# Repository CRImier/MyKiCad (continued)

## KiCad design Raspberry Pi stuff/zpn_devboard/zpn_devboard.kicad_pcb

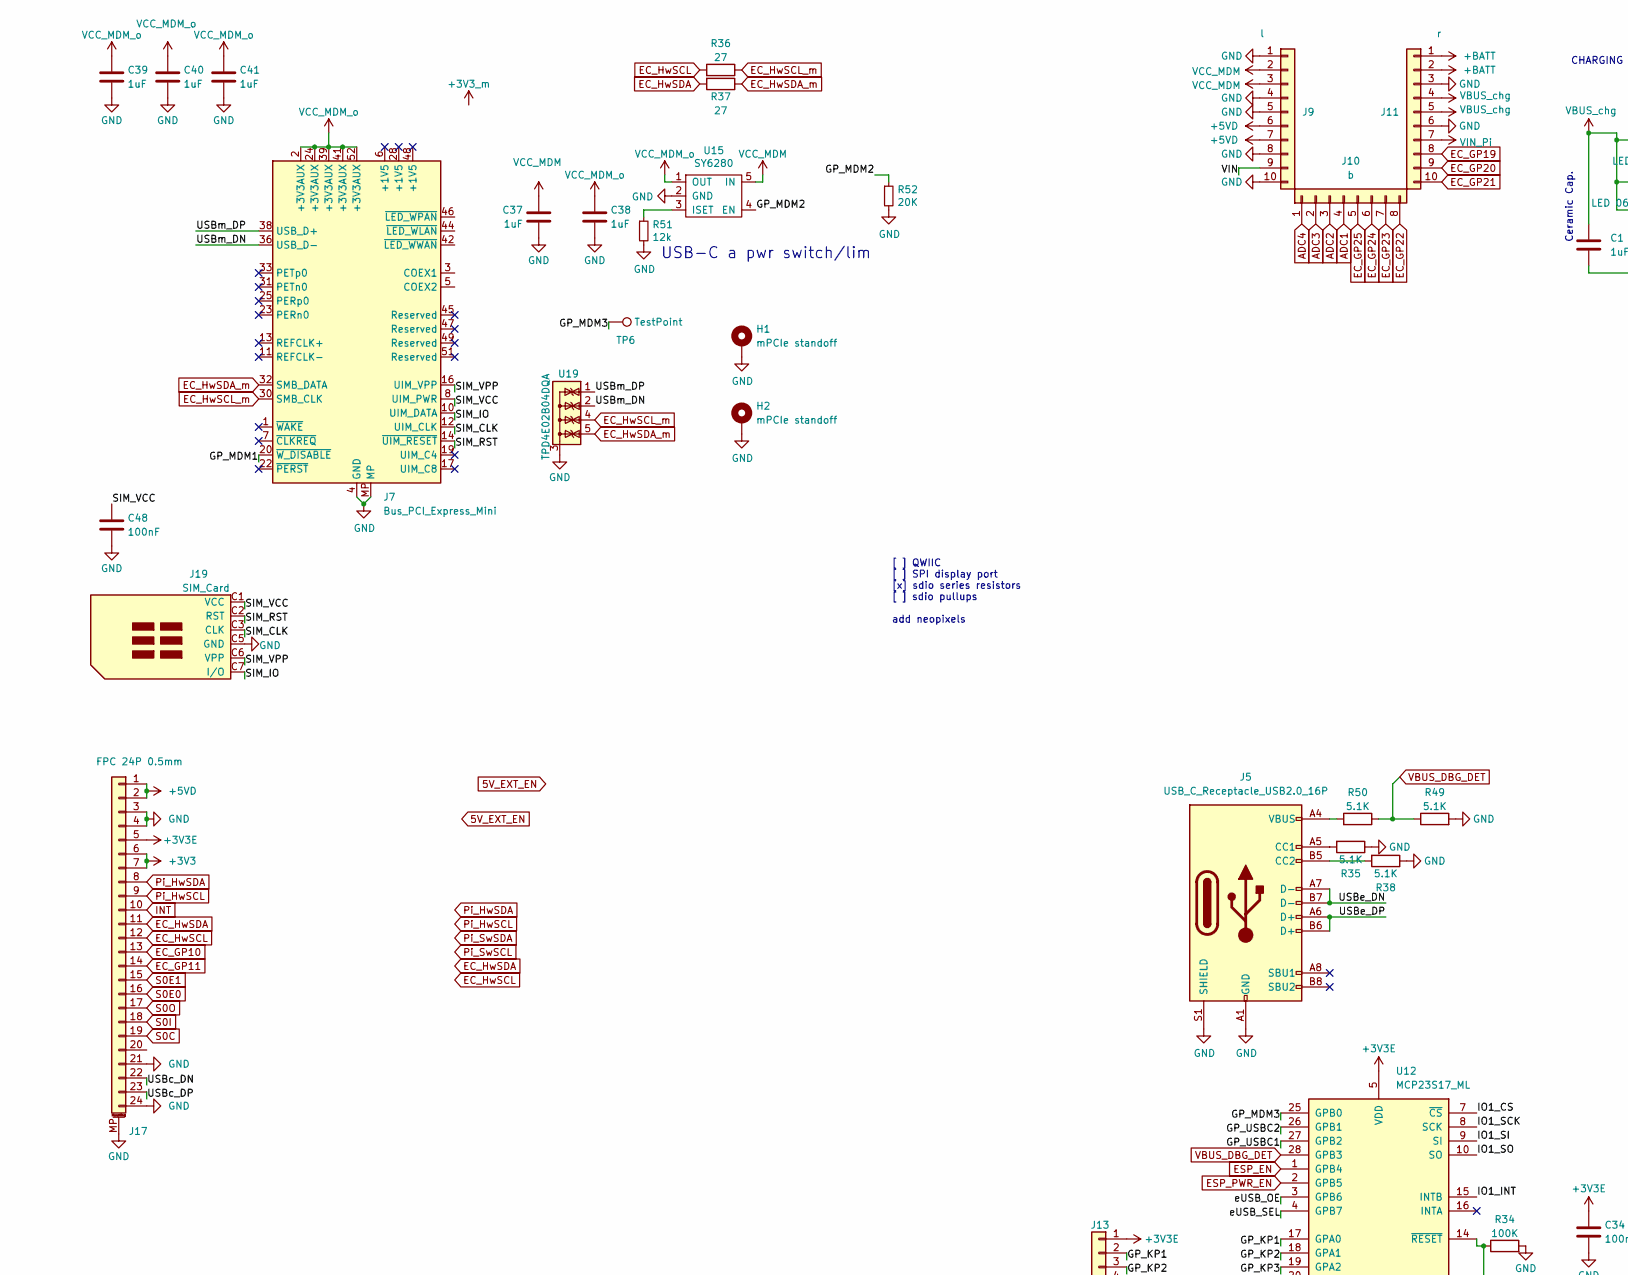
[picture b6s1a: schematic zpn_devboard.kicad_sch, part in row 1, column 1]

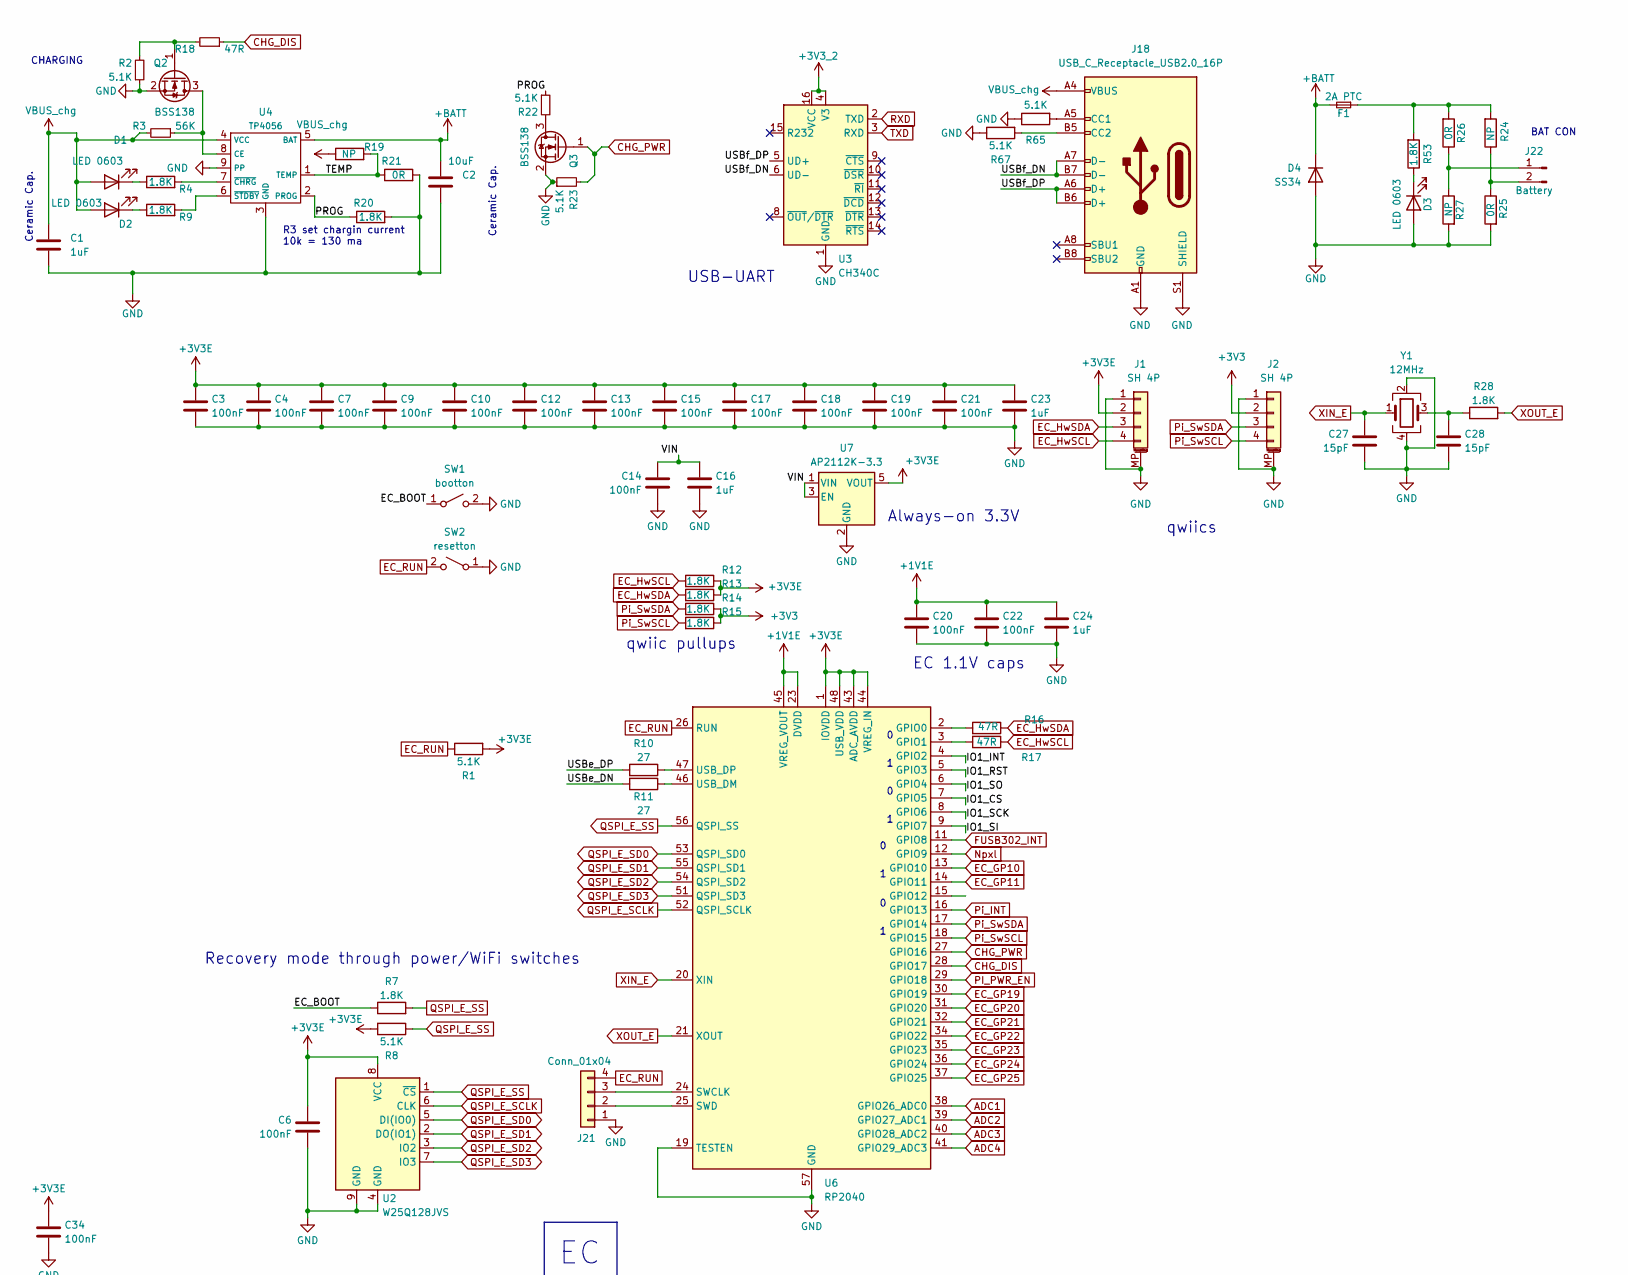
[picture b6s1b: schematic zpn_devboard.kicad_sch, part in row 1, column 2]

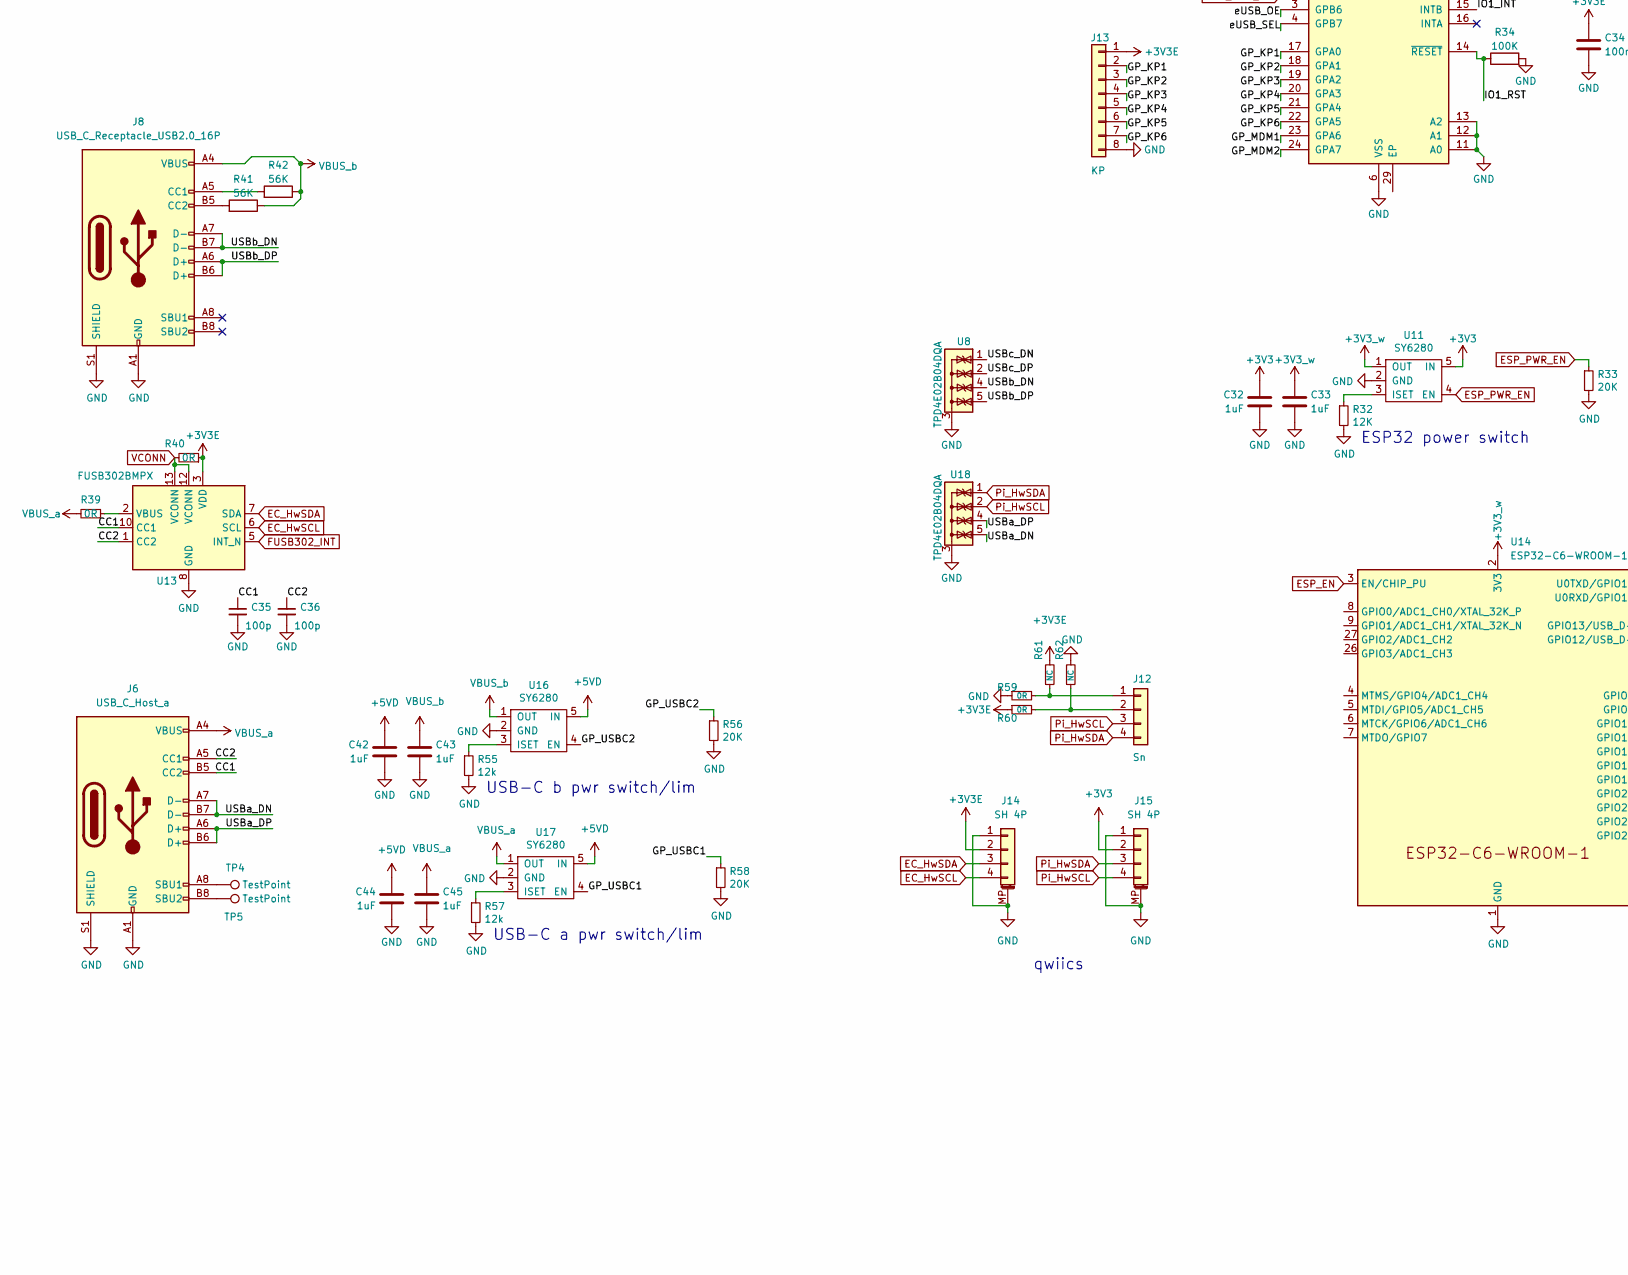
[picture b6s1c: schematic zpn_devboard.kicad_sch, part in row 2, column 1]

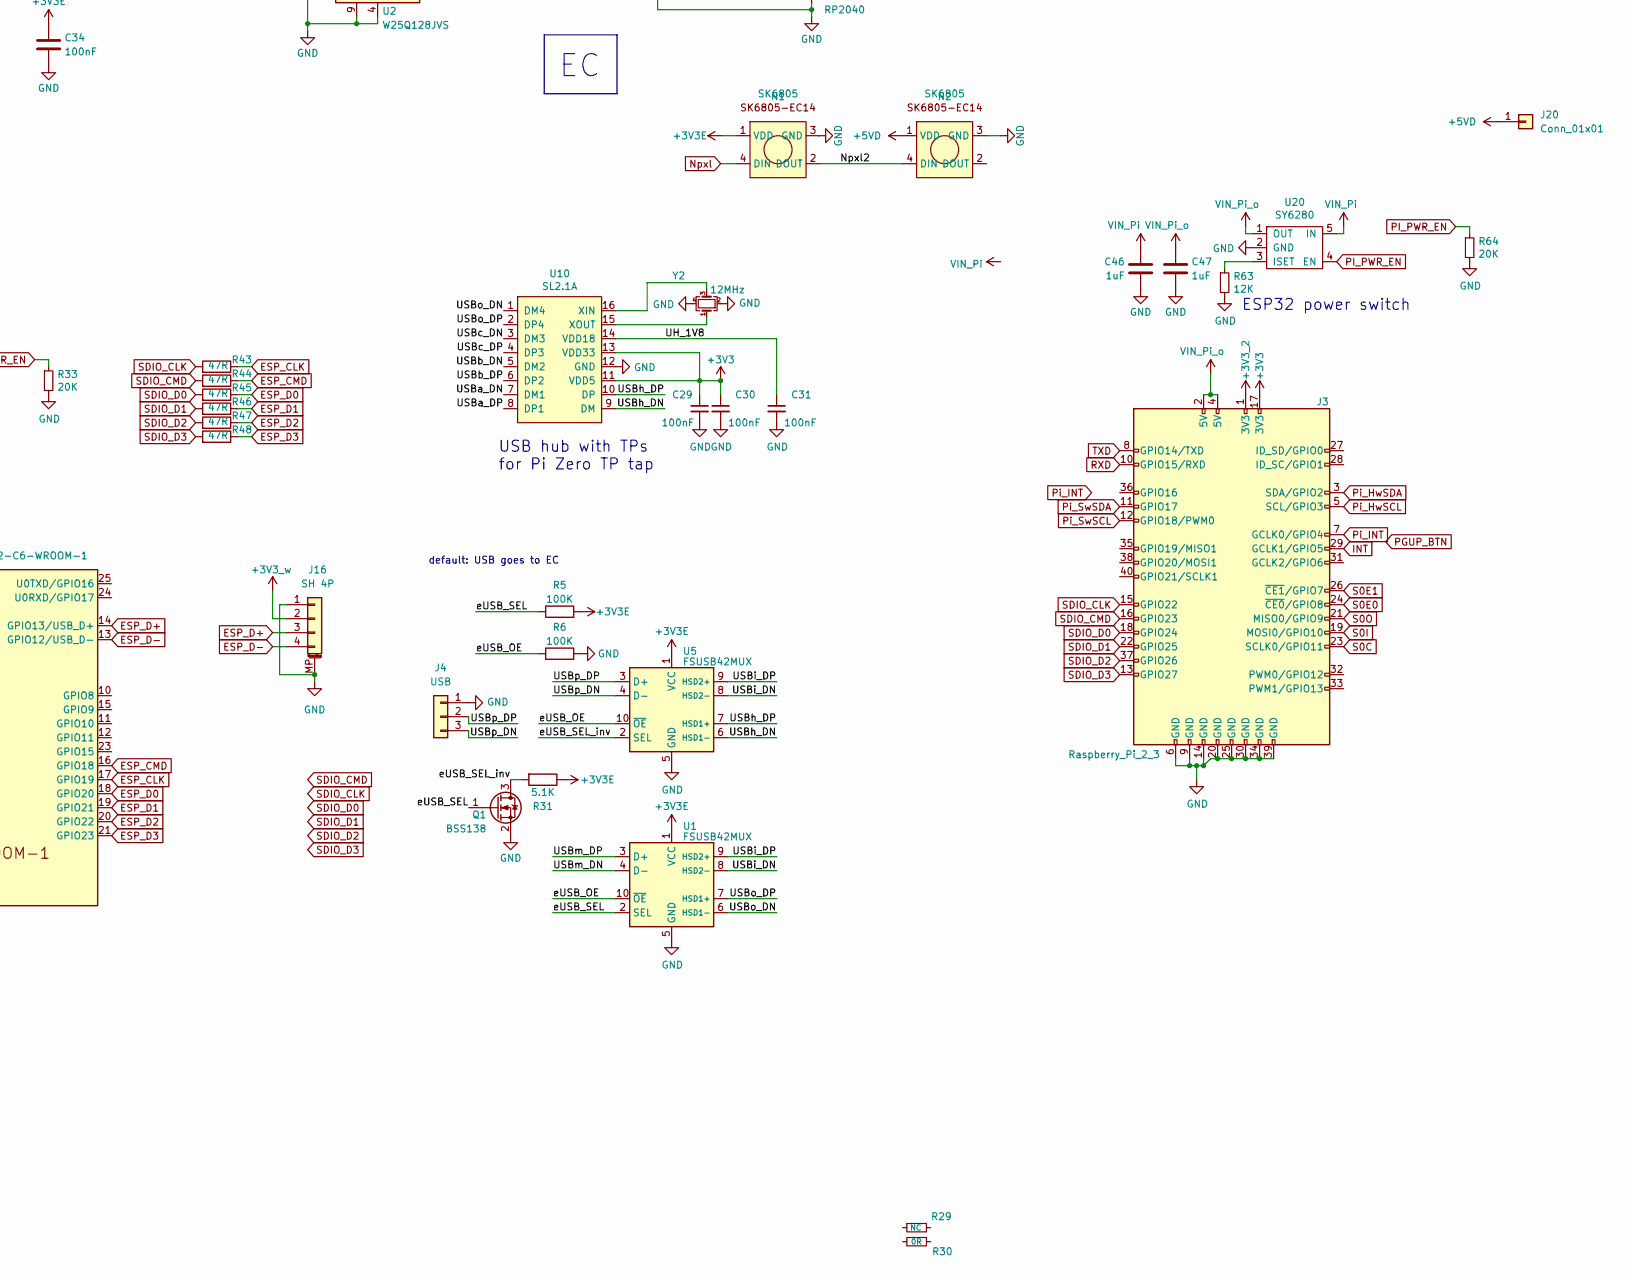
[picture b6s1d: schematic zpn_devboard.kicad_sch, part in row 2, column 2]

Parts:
C1, C16, C23, C24, C32, C33, C37, C38, C39, C40, C41, C42, C43, C44, C45, C46, C47: 1uF; C_0402_1005Metric
C2: 10uF; C_0603_1608Metric
C3, C4, C6, C7, C9, C10, C12, C13, C14, C15, C17, C18, C19, C20, C21, C22, C29, C30, C31, C34, C48: 100nF; C_0402_1005Metric
C27, C28: 15pF; C_0402_1005Metric
C35, C36: 100p; C_0603_1608Metric
D1, D2, D3: LED 0603; LED_0805_2012Metric_Pad1.15x1.40mm_HandSolder
D4: SS34; D_SMA
F1: 2A PTC; Fuse_1206_3216Metric
H1, H2: mPCIe standoff; Standoff_M3_M2.5_Paste
J1, J2, J16: SH 4P; JST_SH_BM04B-SRSS-TB_1x04-1MP_P1.00mm_Vertical
J3: Raspberry_Pi_2_3; Raspberry_Pi_Zero_Socketed_THT_FaceDown_MountingHoles
J4: USB; PinHeader_1x03_P2.54mm_Vertical
J5: USB_C_Receptacle_USB2.0_16P; USB-TYPE-C-TH_TYPEC-300D-BCP16H100
J6: USB_C_Host_a; USB_C_Receptacle_HRO_TYPE-C-31-M-12
J7: Bus_PCI_Express_Mini; BUS_PCI_Express_Mini_Dual
J8, J18: USB_C_Receptacle_USB2.0_16P; USB_C_Receptacle_HRO_TYPE-C-31-M-12
J9: l; PinHeader_1x10_P2.54mm_Vertical
J10: b; PinHeader_1x08_P2.54mm_Vertical
J11: r; PinHeader_1x10_P2.54mm_Vertical
J12: Sn; PinHeader_1x04_P2.54mm_Vertical
J13: KP; PinHeader_2x04_P2.54mm_Vertical
J14, J15: SH 4P; JST_SH_SM04B-SRSS-TB_1x04-1MP_P1.00mm_Horizontal
J17: FPC 24P 0.5mm; Hirose_FH12-24S-0.5SH_1x24-1MP_P0.50mm_Horizontal
J19: SIM_Card; MICROSIM_6P_SMD_HOLDER
J20: Conn_01x01; PinHeader_1x01_P2.54mm_Vertical
J21: Conn_01x04; PinHeader_1x04_P2.54mm_Vertical
J22: Battery; JST_PH_S2B-PH-SM4-TB_1x02-1MP_P2.00mm_Horizontal
N1, N2: SK6805; SK6805-EC14
Q1: BSS138; SOT-23
Q2, Q3: BSS138; SOT-23; LCSC C112239
R1, R2, R8, R22, R23, R31, R35, R38, R49, R50, R65, R67: 5.1K; R_0402_1005Metric
R3, R41, R42: 56K; R_0402_1005Metric
R4, R7, R9, R12, R13, R14, R15, R20, R28, R53: 1.8K; R_0402_1005Metric
R5, R6, R34: 100K; R_0402_1005Metric
R10, R11, R36, R37: 27; R_0402_1005Metric
R16, R17, R18, R43, R44, R45, R46, R47, R48: 47R; R_0402_1005Metric
R19: NP; R_0402_1005Metric
R21, R30, R59, R60: 0R; R_0603_1608Metric_Jumper_Pwr
R24, R27: NP; R_0603_1608Metric
R25, R26: 0R; R_0603_1608Metric_Jumper_PWR
R29, R61, R62: NC; R_0603_1608Metric
R32, R63: 12K; R_0402_1005Metric
R33, R52, R56, R58, R64: 20K; R_0402_1005Metric
R39: 0R; R_0402_1005Metric
R40: 0R; R_0603_1608Metric
R51, R55, R57: 12k; R_0402_1005Metric
SW1: bootton; SW-SMD_4P-L2.8-W1.9-P1.20-LS3.0
SW2: resetton; SW-SMD_4P-L2.8-W1.9-P1.20-LS3.0
TP4, TP5, TP6: TestPoint; TestPoint_Pad_1.0x1.0mm
U1, U5: FSUSB42MUX; MSOP-10_3x3mm_P0.5mm
U2: W25Q128JVS; WSON-8-1EP_6x5mm_P1.27mm_EP3.4x4mm
U3: CH340C; SOIC-16_3.9x9.9mm_P1.27mm
U4: TP4056; SOIC-8-1EP_3.9x4.9mm_P1.27mm_EP2.29x3mm
U6: RP2040; QFN-56-1EP_7x7mm_P0.4mm_EP3.2x3.2mm
U7: AP2112K-3.3; SOT-23-5
U8, U18, U19: TPD4E02B04DQA; USON-10_2.5x1.0mm_P0.5mm
U10: SL2.1A; SO-16_3.9x9.9mm_P1.27mm
U11, U15, U16, U17, U20: SY6280; SOT-23-5
U12: MCP23S17_ML; QFN-28-1EP_6x6mm_P0.65mm_EP4.25x4.25mm
U13: FUSB302BMPX; WQFN-14-1EP_2.5x2.5mm_P0.5mm_EP1.45x1.45mm
U14: ESP32-C6-WROOM-1
Y1, Y2: 12MHz; Crystal_SMD_3225-4Pin_3.2x2.5mm

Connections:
+1V1E: C20.1, C22.1, C24.1, U6.23 (DVDD), U6.45 (VREG_VOUT), U6.50 (DVDD)
+3V3: C29.1, C30.1, C32.1, J2.2, J3.17 (3V3), J15.2, J17.6, J17.7, R14.1, R15.1, U10.11 (VDD5), U10.13 (VDD33), U11.5 (IN)
+3V3E: C3.1, C4.1, C6.1, C7.1, C9.1, C10.1, C12.1, C13.1, C15.1, C17.1, C18.1, C19.1, C21.1, C23.1, C34.1, J1.2, J13.1, J14.2, J17.5, N1.1 (VDD), R1.2, R5.2, R8.2, R12.1, R13.1, R31.1, R40.1, R60.1, R61.2, U1.1 (VCC), U2.8 (VCC), U5.1 (VCC), U6.1 (IOVDD), U6.10 (IOVDD), U6.22 (IOVDD), U6.33 (IOVDD), U6.42 (IOVDD), U6.43 (ADC_AVDD), U6.44 (VREG_IN), U6.48 (USB_VDD), U6.49 (IOVDD), U7.5 (VOUT), U12.5 (VDD), U13.3 (VDD), U13.4 (VDD)
+3V3_2: J3.1 (3V3), U3.4 (V3), U3.16 (VCC)
+3V3_w: C33.1, J16.2, U11.1 (OUT), U14.2 (3V3)
+5VD: C42.1, C44.1, J9.6, J9.7, J17.1, J17.2, J20.1, N2.1 (VDD), U16.5 (IN), U17.5 (IN)
+BATT: C2.1, D4.1 (K), F1.2, J11.1, J11.2, U4.5 (BAT)
/CC1: C35.1, J6.B5 (CC2), U13.10 (CC1), U13.11 (CC1)
/CC2: C36.1, J6.A5 (CC1), U13.1 (CC2), U13.14 (CC2)
/EC_BOOT: R7.1, SW1.1 (A)
/GP_KP1: J13.2, U12.17 (GPA0)
/GP_KP2: J13.3, U12.18 (GPA1)
/GP_KP3: J13.4, U12.19 (GPA2)
/GP_KP4: J13.5, U12.20 (GPA3)
/GP_KP5: J13.6, U12.21 (GPA4)
/GP_KP6: J13.7, U12.22 (GPA5)
/GP_MDM1: J7.20 (~W_DISABLE), U12.23 (GPA6)
/GP_MDM2: R52.1, U12.24 (GPA7), U15.4 (EN)
/GP_MDM3: TP6.1, U12.25 (GPB0)
/GP_USBC1: R58.1, U12.27 (GPB2), U17.4 (EN)
/GP_USBC2: R56.1, U12.26 (GPB1), U16.4 (EN)
/IO1_CS: U6.7 (GPIO5), U12.7 (~CS)
/IO1_INT: U6.4 (GPIO2), U12.15 (INTB)
/IO1_RST: R34.1, U6.5 (GPIO3), U12.14 (~RESET)
/IO1_SCK: U6.8 (GPIO6), U12.8 (SCK)
/IO1_SI: U6.9 (GPIO7), U12.9 (SI)
/IO1_SO: U6.6 (GPIO4), U12.10 (SO)
/Npxl2: N1.2 (DOUT), N2.4 (DIN)
/PROG: R20.1, R22.1, U4.2 (PROG)
/SIM_CLK: J7.12 (UIM_CLK), J19.C3 (CLK)
/SIM_IO: J7.10 (UIM_DATA), J19.C7 (I/O)
/SIM_RST: J7.14 (~UIM_RESET), J19.C2 (RST)
/SIM_VCC: C48.1, J7.8 (UIM_PWR), J19.C1 (VCC)
/SIM_VPP: J7.16 (UIM_VPP), J19.C6 (VPP)
/TEMP: R19.2, R21.1, U4.1 (TEMP)
/UH_1V8: C31.1, U10.14 (VDD18)
/USBa_DN: J6.A7 (D-), J6.B7 (D-), U10.7 (DM1), U18.5 (IO4), U18.6 (NC)
/USBa_DP: J6.A6 (D+), J6.B6 (D+), U10.8 (DP1), U18.4 (IO3), U18.7 (NC)
/USBb_DN: J8.A7 (D-), J8.B7 (D-), U8.4 (IO3), U8.7 (NC), U10.5 (DM2)
/USBb_DP: J8.A6 (D+), J8.B6 (D+), U8.5 (IO4), U8.6 (NC), U10.6 (DP2)
/USBc_DN: J17.22, U8.1 (IO1), U8.10 (NC), U10.3 (DM3)
/USBc_DP: J17.23, U8.2 (IO2), U8.9 (NC), U10.4 (DP3)
/USBe_DN: J5.A7 (D-), J5.B7 (D-), R11.2
/USBe_DP: J5.A6 (D+), J5.B6 (D+), R10.2
/USBf_DN: J18.A7 (D-), J18.B7 (D-), U3.6 (UD-)
/USBf_DP: J18.A6 (D+), J18.B6 (D+), U3.5 (UD+)
/USBh_DN: U5.6 (HSD1-), U10.9 (DM)
/USBh_DP: U5.7 (HSD1+), U10.10 (DP)
/USBi_DN: U1.8 (HSD2-), U5.8 (HSD2-)
/USBi_DP: U1.9 (HSD2+), U5.9 (HSD2+)
/USBm_DN: J7.36 (USB_D-), U1.4 (D-), U19.2 (IO2), U19.9 (NC)
/USBm_DP: J7.38 (USB_D+), U1.3 (D+), U19.1 (IO1), U19.10 (NC)
/USBo_DN: U1.6 (HSD1-), U10.1 (DM4)
/USBo_DP: U1.7 (HSD1+), U10.2 (DP4)
/USBp_DN: J4.3, U5.4 (D-)
/USBp_DP: J4.2, U5.3 (D+)
/VIN: C14.1, C16.1, J9.9, U7.1 (VIN), U7.3 (EN)
/eUSB_OE: R6.1, U1.10 (~OE), U5.10 (~OE), U12.3 (GPB6)
/eUSB_SEL: Q1.1 (G), R5.1, U1.2 (SEL), U12.4 (GPB7)
/eUSB_SEL_inv: Q1.3 (D), R31.2, U5.2 (SEL)
ADC1: J10.4, U6.38 (GPIO26_ADC0)
ADC2: J10.3, U6.39 (GPIO27_ADC1)
ADC3: J10.2, U6.40 (GPIO28_ADC2)
ADC4: J10.1, U6.41 (GPIO29_ADC3)
CHG_DIS: R18.1, U6.28 (GPIO17)
CHG_PWR: Q3.1 (G), R23.2, U6.27 (GPIO16)
EC_GP10: J17.13, U6.13 (GPIO10)
EC_GP11: J17.14, U6.14 (GPIO11)
EC_GP19: J11.8, U6.30 (GPIO19)
EC_GP20: J11.9, U6.31 (GPIO20)
EC_GP21: J11.10, U6.32 (GPIO21)
EC_GP22: J10.8, U6.34 (GPIO22)
EC_GP23: J10.7, U6.35 (GPIO23)
EC_GP24: J10.6, U6.36 (GPIO24)
EC_GP25: J10.5, U6.37 (GPIO25)
EC_HwSCL: J1.4, J14.4, J17.12, R12.2, R17.1, R36.2, U13.6 (SCL)
EC_HwSCL_m: J7.30 (SMB_CLK), R36.1, U19.4 (IO3), U19.7 (NC)
EC_HwSDA: J1.3, J14.3, J17.11, R13.2, R16.1, R37.2, U13.7 (SDA)
EC_HwSDA_m: J7.32 (SMB_DATA), R37.1, U19.5 (IO4), U19.6 (NC)
EC_RUN: J21.4, R1.1, SW2.2 (B), U6.26 (RUN)
ESP_CLK: R43.1, U14.17 (GPIO19)
ESP_CMD: R44.1, U14.16 (GPIO18)
ESP_D0: R45.1, U14.18 (GPIO20)
ESP_D1: R46.1, U14.19 (GPIO21)
ESP_D2: R47.1, U14.20 (GPIO22)
ESP_D3: R48.1, U14.21 (GPIO23)
ESP_D+: J16.3, U14.14 (GPIO13/USB_D+)
ESP_D-: J16.4, U14.13 (GPIO12/USB_D-)
ESP_EN: U12.1 (GPB4), U14.3 (EN/CHIP_PU)
ESP_PWR_EN: R33.1, U11.4 (EN), U12.2 (GPB5)
FUSB302_INT: U6.11 (GPIO8), U13.5 (INT_N)
GND: C1.2, C2.2, C3.2, C4.2, C6.2, C7.2, C9.2, C10.2, C12.2, C13.2, C14.2, C15.2, C16.2, C17.2, C18.2, C19.2, C20.2, C21.2, C22.2, C23.2, C24.2, C27.2, C28.2, C29.2, C30.2, C31.2, C32.2, C33.2, C34.2, C35.2, C36.2, C37.2, C38.2, C39.2, C40.2, C41.2, C42.2, C43.2, C44.2, C45.2, C46.2, C47.2, C48.2, D3.2 (A), D4.2 (A), H1.1, H2.1, J1.1, J1.MP (MountPin), J2.1, J2.MP (MountPin), J3.6 (GND), J3.9 (GND), J3.14 (GND), J3.20 (GND), J3.25 (GND), J3.30 (GND), J3.34 (GND), J3.39 (GND), J4.1, J5.A1 (GND), J5.A12 (GND), J5.B1 (GND), J5.B12 (GND), J5.S1 (SHIELD), J6.A1 (GND), J6.A12 (GND), J6.B1 (GND), J6.B12 (GND), J6.S1 (SHIELD), J7.4 (GND), J7.9 (GND), J7.15 (GND), J7.18 (GND), J7.21 (GND), J7.26 (GND), J7.27 (GND), J7.29 (GND), J7.34 (GND), J7.35 (GND), J7.37 (GND), J7.40 (GND), J7.43 (GND), J7.50 (GND), J7.MP, J8.A1 (GND), J8.A12 (GND), J8.B1 (GND), J8.B12 (GND), J8.S1 (SHIELD), J9.1, J9.4, J9.5, J9.8, J9.10, J11.3, J11.6, J13.8, J14.1, J14.MP (MountPin), J15.1, J15.MP (MountPin), J16.1, J16.MP (MountPin), J17.3, J17.4, J17.21, J17.24, J17.MP (MountPin), J18.A1 (GND), J18.A12 (GND), J18.B1 (GND), J18.B12 (GND), J18.S1 (SHIELD), J19.C5 (GND), J21.1, N1.3 (GND), N2.3 (GND), Q1.2 (S), Q2.2 (S), Q3.2 (S), R2.1, R6.2, R20.2, R21.2, R23.1, R25.2, R27.2, R32.2, R33.2, R34.2, R35.1, R38.1, R49.2, R51.2, R52.2, R55.2, R56.2, R57.2, R58.2, R59.1, R62.2, R63.2, R64.2, R65.1, R67.1, SW1.2 (B), SW2.1 (A), U1.5 (GND), U2.4 (GND), U2.9 (GND), U3.1 (GND), U4.3 (GND), U4.9 (PP), U5.5 (GND), U6.19 (TESTEN), U6.57 (GND), U7.2 (GND), U8.3 (G), U8.8 (G), U10.12 (GND), U11.2 (GND), U12.6 (VSS), U12.11 (A0), U12.12 (A1), U12.13 (A2), U13.8 (GND), U13.9 (GND), U13.15 (GND), U14.1 (GND), U14.28 (GND), U14.29 (GND), U15.2 (GND), U16.2 (GND), U17.2 (GND), U18.3 (G), U18.8 (G), U19.3 (G), U19.8 (G), U20.2 (GND), Y1.2, Y1.4, Y2.2, Y2.4
INT: J3.29 (GCLK1/GPIO5), J17.10
unnamed: C28.1, R28.1, Y1.3
unnamed: D1.1 (K), R4.1
unnamed: D2.1 (K), R9.1
unnamed: D3.1 (K), R53.1
unnamed: F1.1, R24.2, R26.2, R53.2
unnamed: J5.A5 (CC1), R35.2
unnamed: J5.B5 (CC2), R38.2
unnamed: J5.A4 (VBUS), J5.A9 (VBUS), J5.B4 (VBUS), J5.B9 (VBUS), R50.2
unnamed: J6.A8 (SBU1), TP4.1
unnamed: J6.B8 (SBU2), TP5.1
unnamed: J8.A5 (CC1), R42.2
unnamed: J8.B5 (CC2), R41.2
unnamed: J12.1, R59.2, R61.1
unnamed: J12.2, R60.2, R62.1
unnamed: J18.A5 (CC1), R65.2
unnamed: J18.B5 (CC2), R67.2
unnamed: J21.2, U6.25 (SWD)
unnamed: J21.3, U6.24 (SWCLK)
unnamed: J22.1, R26.1, R27.1
unnamed: J22.2, R24.1, R25.1
unnamed: Q2.3 (D), R3.1, U4.8 (CE)
unnamed: Q2.1 (G), R2.2, R18.2
unnamed: Q3.3 (D), R22.2
unnamed: R4.2, U4.7 (~CHRG)
unnamed: R9.2, U4.6 (~STDBY)
unnamed: R16.2, U6.2 (GPIO0)
unnamed: R17.2, U6.3 (GPIO1)
unnamed: R11.1, U6.46 (USB_DM)
unnamed: R10.1, U6.47 (USB_DP)
unnamed: U10.16 (XIN), Y2.3
unnamed: U10.15 (XOUT), Y2.1
unnamed: R32.1, U11.3 (ISET)
unnamed: R39.1, U13.2 (VBUS)
unnamed: R51.1, U15.3 (ISET)
unnamed: R55.1, U16.3 (ISET)
unnamed: R57.1, U17.3 (ISET)
unnamed: R63.1, U20.3 (ISET)
Npxl: N1.4 (DIN), U6.12 (GPIO9)
PI_PWR_EN: R64.1, U6.29 (GPIO18), U20.4 (EN)
Pi_HwSCL: J3.5 (SCL/GPIO3), J12.3, J15.4, J17.9, U18.2 (IO2), U18.9 (NC)
Pi_HwSDA: J3.3 (SDA/GPIO2), J12.4, J15.3, J17.8, U18.1 (IO1), U18.10 (NC)
Pi_INT: J3.7 (GCLK0/GPIO4), U6.16 (GPIO13)
Pi_SwSCL: J2.4, J3.12 (GPIO18/PWM0), R15.2, U6.18 (GPIO15)
Pi_SwSDA: J2.3, J3.11 (GPIO17), R14.2, U6.17 (GPIO14)
QSPI_E_SCLK: U2.6 (CLK), U6.52 (QSPI_SCLK)
QSPI_E_SD0: U2.5 (DI(IO0)), U6.53 (QSPI_SD0)
QSPI_E_SD1: U2.2 (DO(IO1)), U6.55 (QSPI_SD1)
QSPI_E_SD2: U2.3 (IO2), U6.54 (QSPI_SD2)
QSPI_E_SD3: U2.7 (IO3), U6.51 (QSPI_SD3)
QSPI_E_SS: R7.2, R8.1, U2.1 (~CS), U6.56 (QSPI_SS)
RXD: J3.10 (GPIO15/RXD), U3.2 (TXD)
S0C: J3.23 (SCLK0/GPIO11), J17.19
S0E0: J3.24 (~CE0/GPIO8), J17.16
S0E1: J3.26 (~CE1/GPIO7), J17.15
S0I: J3.19 (MOSI0/GPIO10), J17.18
S0O: J3.21 (MISO0/GPIO9), J17.17
SDIO_CLK: J3.15 (GPIO22), R43.2
SDIO_CMD: J3.16 (GPIO23), R44.2
SDIO_D0: J3.18 (GPIO24), R45.2
SDIO_D1: J3.22 (GPIO25), R46.2
SDIO_D2: J3.37 (GPIO26), R47.2
SDIO_D3: J3.13 (GPIO27), R48.2
TXD: J3.8 (GPIO14/TXD), U3.3 (RXD)
VBUS_DBG_DET: R49.1, R50.1, U12.28 (GPB3)
VBUS_a: C45.1, J6.A4 (VBUS), J6.A9 (VBUS), J6.B4 (VBUS), J6.B9 (VBUS), R39.2, U17.1 (OUT)
VBUS_b: C43.1, J8.A4 (VBUS), J8.A9 (VBUS), J8.B4 (VBUS), J8.B9 (VBUS), R41.1, R42.1, U16.1 (OUT)
VBUS_chg: C1.1, D1.2 (A), D2.2 (A), J11.4, J11.5, J18.A4 (VBUS), J18.A9 (VBUS), J18.B4 (VBUS), J18.B9 (VBUS), R3.2, R19.1, U4.4 (VCC)
VCC_MDM: C37.1, J9.2, J9.3, U15.5 (IN)
VCC_MDM_o: C38.1, C39.1, C40.1, C41.1, J7.2 (+3V3AUX), J7.24 (+3V3AUX), J7.39 (+3V3AUX), J7.41 (+3V3AUX), J7.52 (+3V3AUX), U15.1 (OUT)
VCONN: R40.2, U13.12 (VCONN), U13.13 (VCONN)
VIN_Pi: C46.1, J11.7, U20.5 (IN)
VIN_Pi_o: C47.1, J3.2 (5V), J3.4 (5V), U20.1 (OUT)
XIN_E: C27.1, U6.20 (XIN), Y1.1
XOUT_E: R28.2, U6.21 (XOUT)

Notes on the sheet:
USB-C a pwr switch/lim
qwiics
USB-C b pwr switch/lim
Always-on 3.3V
USB hub with TPs for Pi Zero TP tap
qwiic pullups
CHARGING
R3 set chargin current 10k = 130 ma
EC 1.1V caps
USB-UART
ESP32 power switch
Ceramic Cap.
default: USB goes to EC
[ ] QWIIC [ ] SPI display port [x] sdio series resistors [ ] sdio pullups add neopixels
BAT CON
Recovery mode through power/WiFi switches

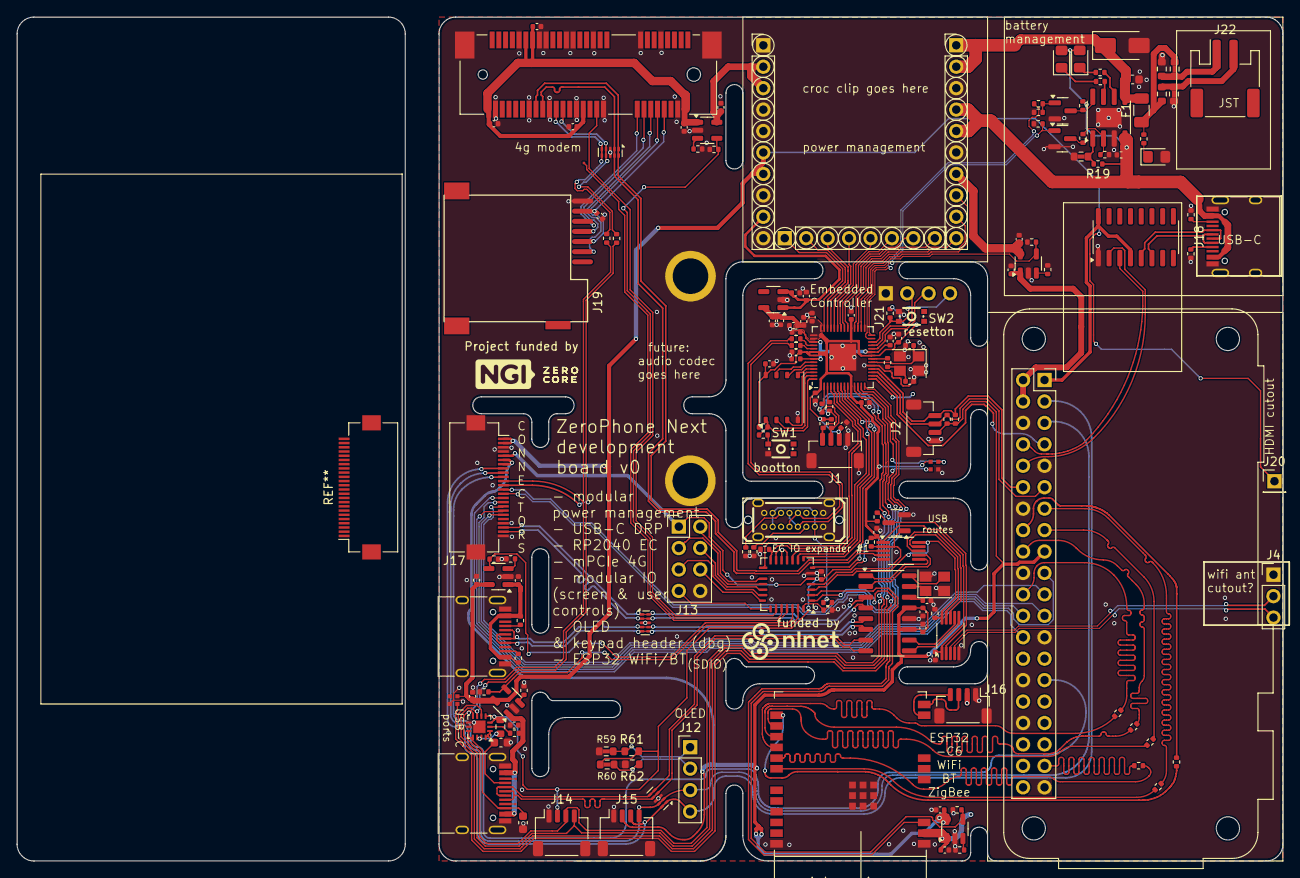
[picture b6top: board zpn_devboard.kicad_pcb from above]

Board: 4 copper layers, 100.0 x 100.0 mm, 166 parts (0 on the bottom side), 167 nets.

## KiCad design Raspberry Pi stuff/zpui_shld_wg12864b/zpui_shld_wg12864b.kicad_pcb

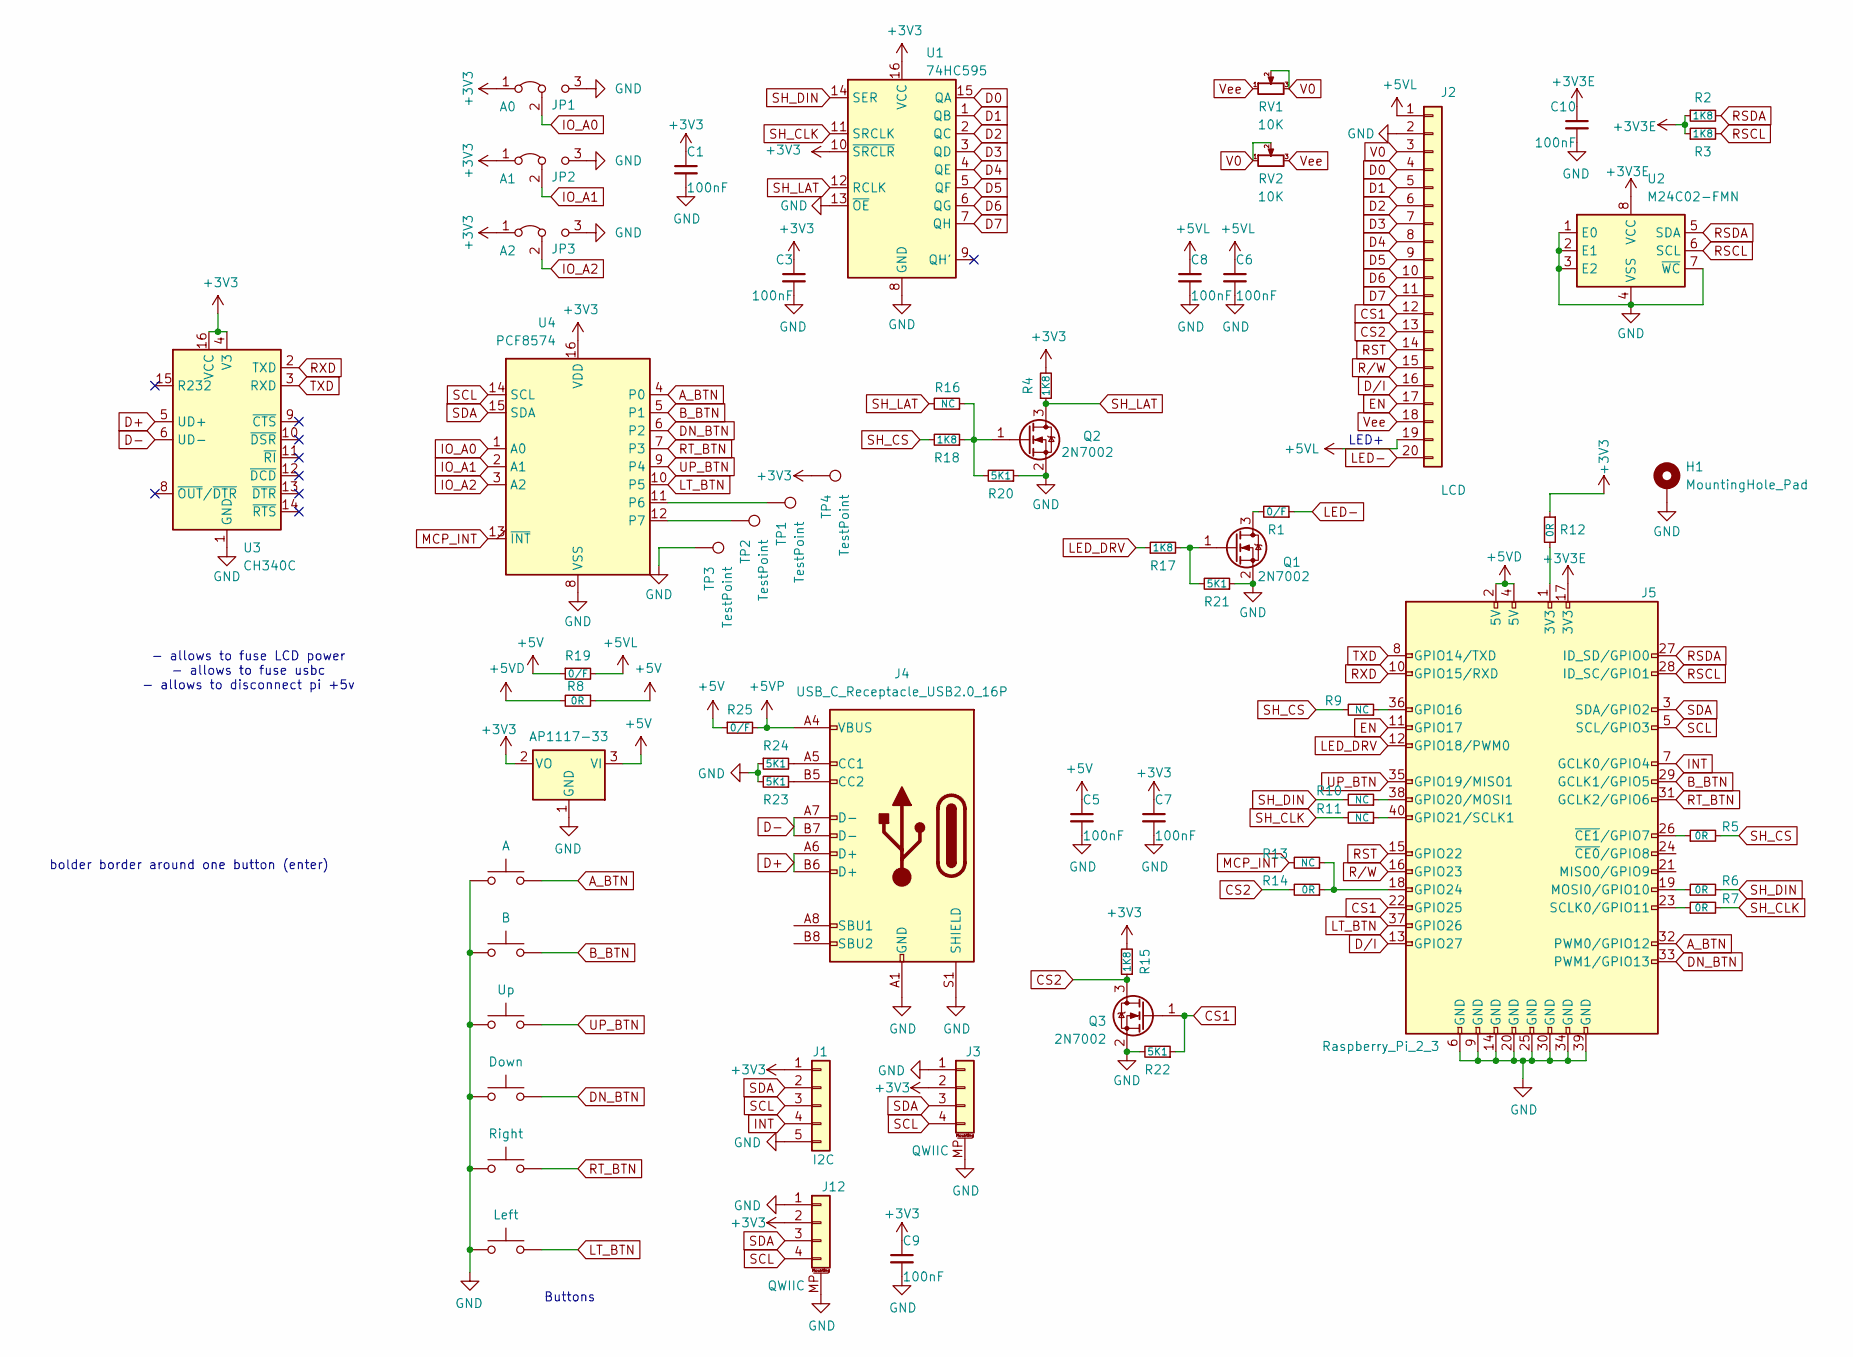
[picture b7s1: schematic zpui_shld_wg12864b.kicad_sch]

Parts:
C1, C3, C5, C6, C7, C8, C9, C10: 100nF; C_0603_1608Metric
H1: MountingHole_Pad; MountingHole_3mm_Pad
J1: I2C; PinHeader_1x05_P2.54mm_Vertical
J2: LCD; PinHeader_1x20_P2.54mm_Vertical
J3, J12: QWIIC; JST_SH_SM04B-SRSS-TB_1x04-1MP_P1.00mm_Horizontal
J4: USB_C_Receptacle_USB2.0_16P; USB_C_Receptacle_HRO_TYPE-C-31-M-12
J5: Raspberry_Pi_2_3; RASPBERRY_PI_HAT
JP1: A0; SolderJumper-3_P1.3mm_Bridged12_Pad1.0x1.5mm
JP2: A1; SolderJumper-3_P1.3mm_Bridged12_Pad1.0x1.5mm
JP3: A2; SolderJumper-3_P1.3mm_Bridged12_Pad1.0x1.5mm
Q1, Q2, Q3: 2N7002; SOT-23
R1, R19, R25: 0/F; R_0805_2012Metric
R2, R3, R4, R15, R17, R18: 1K8; R_0603_1608Metric
R5, R6, R7, R8, R12, R14: 0R; R_0603_1608Metric_Jumper
R9, R10, R11, R13, R16: NC; R_0603_1608Metric
R20, R21, R22, R23, R24: 5K1; R_0603_1608Metric
RV1: 10K; RES-ADJ-TH_VZ067TL1B202
RV2: 10K; Potentiometer_Bourns_3314J_Vertical
SW1: A; SW_SPST_PTS645; LCSC Part # C285456
SW2: B; SW_SPST_PTS645; mpn REQUIRED https://www.lcsc.com/product-d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; LCSC Part # C285456
SW3: Up; SW_SPST_PTS645; mpn REQUIRED https://www.lcsc.com/product-d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; LCSC Part # C285456
SW4: Down; SW_SPST_PTS645; mpn REQUIRED https://www.lcsc.com/product-d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; LCSC Part # C285456
SW5: Right; SW_SPST_PTS645; mpn REQUIRED https://www.lcsc.com/product-d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; LCSC Part # C285456
SW6: Left; SW_SPST_PTS645; mpn REQUIRED https://www.lcsc.com/product-d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; LCSC Part # C285456
TP1, TP2, TP3, TP4: TestPoint; TestPoint_Pad_2.0x2.0mm
U1: 74HC595; SO-16_3.9x9.9mm_P1.27mm
U2: M24C02-FMN; SOIC-8_3.9x4.9mm_P1.27mm
U3: CH340C; SOIC-16_3.9x9.9mm_P1.27mm
U4: PCF8574; SOIC-16W_7.5x10.3mm_P1.27mm
U5: AP1117-33; SOT-223-3_TabPin2

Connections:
+3V3: C1.1, C3.1, C7.1, C9.1, J1.1, J3.2, J12.2, JP1.1 (A), JP2.1 (A), JP3.1 (A), R4.2, R12.1, R15.2, TP4.1, U1.10 (~SRCLR), U1.16 (VCC), U3.4 (V3), U3.16 (VCC), U4.16 (VDD), U5.2 (VO)
+3V3E: C10.1, J5.17 (3V3), R2.1, R3.1, U2.8 (VCC)
+5V: C5.1, R8.1, R19.1, R25.1, U5.3 (VI)
+5VD: J5.2 (5V), J5.4 (5V), R8.2
+5VL: C6.1, C8.1, J2.1, J2.19, R19.2
+5VP: J4.A4 (VBUS), J4.A9 (VBUS), J4.B4 (VBUS), J4.B9 (VBUS), R25.2
A_BTN: J5.32 (PWM0/GPIO12), SW1.1, U4.4 (P0)
B_BTN: J5.29 (GCLK1/GPIO5), SW2.1, U4.5 (P1)
CS1: J2.12, J5.22 (GPIO25), Q3.1 (G), R22.1
CS2: J2.13, Q3.3 (D), R14.2, R15.1
D0: J2.4, U1.15 (QA)
D1: J2.5, U1.1 (QB)
D2: J2.6, U1.2 (QC)
D3: J2.7, U1.3 (QD)
D4: J2.8, U1.4 (QE)
D5: J2.9, U1.5 (QF)
D6: J2.10, U1.6 (QG)
D7: J2.11, U1.7 (QH)
D+: J4.A6 (D+), J4.B6 (D+), U3.5 (UD+)
D-: J4.A7 (D-), J4.B7 (D-), U3.6 (UD-)
DN_BTN: J5.33 (PWM1/GPIO13), SW4.1, U4.6 (P2)
D/I: J2.16, J5.13 (GPIO27)
EN: J2.17, J5.11 (GPIO17)
GND: C1.2, C3.2, C5.2, C6.2, C7.2, C8.2, C9.2, C10.2, H1.1, J1.5, J2.2, J3.1, J3.MP (MountPin), J4.A1 (GND), J4.A12 (GND), J4.B1 (GND), J4.B12 (GND), J4.S1 (SHIELD), J5.6 (GND), J5.9 (GND), J5.14 (GND), J5.20 (GND), J5.25 (GND), J5.30 (GND), J5.34 (GND), J5.39 (GND), J12.1, J12.MP (MountPin), JP1.3 (B), JP2.3 (B), JP3.3 (B), Q1.2 (S), Q2.2 (S), Q3.2 (S), R20.1, R21.1, R22.2, R23.2, R24.1, SW1.2, SW2.2, SW3.2, SW4.2, SW5.2, SW6.2, TP3.1, U1.8 (GND), U1.13 (~OE), U2.1 (E0), U2.2 (E1), U2.3 (E2), U2.4 (VSS), U2.7 (~WC), U3.1 (GND), U4.8 (VSS), U5.1 (GND)
INT: J1.4, J5.7 (GCLK0/GPIO4)
IO_A0: JP1.2 (C), U4.1 (A0)
IO_A1: JP2.2 (C), U4.2 (A1)
IO_A2: JP3.2 (C), U4.3 (A2)
LED-: J2.20, R1.1
LED_DRV: J5.12 (GPIO18/PWM0), R17.1
LT_BTN: J5.37 (GPIO26), SW6.1, U4.10 (P5)
MCP_INT: R13.2, U4.13 (~INT)
unnamed: J4.A5 (CC1), R24.2
unnamed: J4.B5 (CC2), R23.1
unnamed: J5.1 (3V3), R12.2
unnamed: J5.36 (GPIO16), R9.1
unnamed: J5.38 (GPIO20/MOSI1), R10.1
unnamed: J5.40 (GPIO21/SCLK1), R11.1
unnamed: J5.18 (GPIO24), R13.1, R14.1
unnamed: J5.19 (MOSI0/GPIO10), R6.1
unnamed: J5.23 (SCLK0/GPIO11), R7.1
unnamed: J5.26 (~CE1/GPIO7), R5.1
unnamed: Q1.3 (D), R1.2
unnamed: Q1.1 (G), R17.2, R21.2
unnamed: Q2.1 (G), R16.1, R18.1, R20.2
unnamed: TP1.1, U4.11 (P6)
unnamed: TP2.1, U4.12 (P7)
RSCL: J5.28 (ID_SC/GPIO1), R3.2, U2.6 (SCL)
RSDA: J5.27 (ID_SD/GPIO0), R2.2, U2.5 (SDA)
RST: J2.14, J5.15 (GPIO22)
RT_BTN: J5.31 (GCLK2/GPIO6), SW5.1, U4.7 (P3)
RXD: J5.10 (GPIO15/RXD), U3.2 (TXD)
R/W: J2.15, J5.16 (GPIO23)
SCL: J1.3, J3.4, J5.5 (SCL/GPIO3), J12.4, U4.14 (SCL)
SDA: J1.2, J3.3, J5.3 (SDA/GPIO2), J12.3, U4.15 (SDA)
SH_CLK: R7.2, R11.2, U1.11 (SRCLK)
SH_CS: R5.2, R9.2, R18.2
SH_DIN: R6.2, R10.2, U1.14 (SER)
SH_LAT: Q2.3 (D), R4.1, R16.2, U1.12 (RCLK)
TXD: J5.8 (GPIO14/TXD), U3.3 (RXD)
UP_BTN: J5.35 (GPIO19/MISO1), SW3.1, U4.9 (P4)
V0: J2.3, RV1.2, RV1.3, RV2.1, RV2.2
Vee: J2.18, RV1.1, RV2.3

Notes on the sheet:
- allows to fuse LCD power - allows to fuse usbc - allows to disconnect pi +5v
Buttons
LED+
bolder border around one button (enter)
